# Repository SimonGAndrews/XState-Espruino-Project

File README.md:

# XState-Espruino-Project

This public umbrella repository records the development of three approaches to
running state machines and statecharts on
[Espruino](https://www.espruino.com/), informed by
[XState](https://github.com/statelyai/xstate).

It retains the flat FSM baseline, the JavaScript FSMPlus engine, shared
examples, architectural decisions, and the history connecting those
approaches. The native C engine, XFSM, matured through this project and is now
developed independently in the standalone
[`SimonGAndrews/Espruino-XFSM`](https://github.com/SimonGAndrews/Espruino-XFSM)
repository.

This repository remains public as a project history, comparison point, and
navigation hub. Each implementation direction retains its own behavioural
authority and development lifecycle.

## Current Status

XFSM is the current active development focus. Its source, specifications,
tests, evidence, examples, and integration guidance are maintained in the
standalone Espruino-XFSM repository. Its
[implementation status](https://github.com/SimonGAndrews/Espruino-XFSM/blob/main/docs/implementation-status.md)
records current qualification and development work.

Stage 1 remains the compact flat embedded baseline. FSMPlus remains a working
JavaScript hierarchical engine that can be deployed without a custom Espruino
firmware build. Moving XFSM to its own repository does not replace or deprecate
either direction.

The [current project context](docs/project-context.md) identifies the authority
and compatibility references for all three directions.

## Project Outcomes

The stage numbers describe the order in which the approaches arose. They do
not define a replacement sequence.

| Direction | Outcome | Current position |
| --- | --- | --- |
| [Stage 1: `xstate-fsm-espruino`](projects/xstate-fsm-espruino/) | Compact flat FSM adapted from `@xstate/fsm` for Espruino | Retained as a separate Git submodule and embedded baseline |
| [Stage 2: `xstate-fsmPlus`](projects/xstate-fsmPlus/) | Hierarchical JavaScript engine supporting compound states | Working parallel implementation maintained in this repository |
| [Stage 3: `Espruino-XFSM`](https://github.com/SimonGAndrews/Espruino-XFSM) | Specification-led native C hierarchical engine exposed through Espruino's `XFSM` module | Active development in its standalone repository |

Together, these approaches explored the trade-offs between deployment
simplicity, statechart capability, memory use, execution cost, and integration
with Espruino internals.

## What Remains Here

The umbrella repository retains:

- the Stage 1 Git submodule and its separate history
- the canonical FSMPlus implementation, tests, and status documents
- shared application examples and scenario-driven testing material
- architectural decisions and the background to the three approaches
- the XState v4 reference runner used by Stage 1 and FSMPlus work
- an archived XState v4.38.3 source tree for historical reference
- the XFSM journey and relocation record

Material shared by the projects is evidence or a reusable input. It does not
automatically change the behavioural contract of another implementation.

## XFSM Relocation

Current XFSM work belongs in
[`SimonGAndrews/Espruino-XFSM`](https://github.com/SimonGAndrews/Espruino-XFSM).
The standalone repository is the source of truth for the native library,
Profile 2 specification, tests, recorded evidence, examples, and development
workflow. Its canonical `xfsm/` library is exported unchanged into Espruino's
`libs/xfsm/` directory for integration builds.

This umbrella retains a permanent
[`projects/Xstate-fsm-c/`](projects/Xstate-fsm-c/) placeholder explaining the
project's journey and current location. The last complete umbrella copy is
preserved by the
[`xfsm-umbrella-snapshot-final`](https://github.com/SimonGAndrews/XState-Espruino-Project/tree/xfsm-umbrella-snapshot-final/projects/Xstate-fsm-c)
tag.

## Testing And Authority

Testing across the umbrella project is scenario-driven and trace-based, using
deterministic event sequences and observable state, action, and context
results. The shared [testing strategy](docs/governance/testing-strategy.md)
describes this approach.

Each implementation decides which shared scenarios it adopts and which
external references define its expected behaviour:

- Stage 1 is governed by its submodule source, tests, and documentation.
- FSMPlus is governed by its implementation, tests, status, and applicable
  architectural decisions in this repository.
- XFSM is governed by the standalone Profile 2 specification and its
  incorporated Profile 1 and history requirements.

The [project context](docs/project-context.md) is the complete navigation and
authority guide.

## Documentation

- [Current project context and authority](docs/project-context.md)
- [Background and evolution](docs/governance/background.md)
- [Testing strategy and issue ownership](docs/governance/testing-strategy.md)
- [FSMPlus status and backlog](docs/governance/fsmPlus-status-01.md)
- [Architectural decisions](docs/decisions/)
- [Reference links](docs/references/links.md)
- [XFSM project overview](https://github.com/SimonGAndrews/Espruino-XFSM#readme)
- [XFSM Profile 2 specification](https://github.com/SimonGAndrews/Espruino-XFSM/blob/main/docs/specification-profile-2.md)
- [XFSM implementation status](https://github.com/SimonGAndrews/Espruino-XFSM/blob/main/docs/implementation-status.md)
- [XFSM Espruino integration workflow](https://github.com/SimonGAndrews/Espruino-XFSM/blob/main/docs/espruino-integration.md)

## Licensing

This umbrella repository contains independently licensed projects, an upstream
source archive, and a Git submodule. See [LICENSING.md](LICENSING.md) for the
path-to-licence map. The retained Xstate-fsm-c record and tagged snapshot are
licensed under MPL-2.0. The standalone Espruino-XFSM repository publishes its
own path-based licensing map.

## Acknowledgements

- **Espruino** - the [open-source JavaScript runtime](https://www.espruino.com/)
  and community that make embedded JavaScript development possible.
- **XState and Stately** - the statechart model, tooling, and API patterns from
  [XState](https://github.com/statelyai/xstate) and
  [Stately](https://stately.ai/) that informed the three project directions.

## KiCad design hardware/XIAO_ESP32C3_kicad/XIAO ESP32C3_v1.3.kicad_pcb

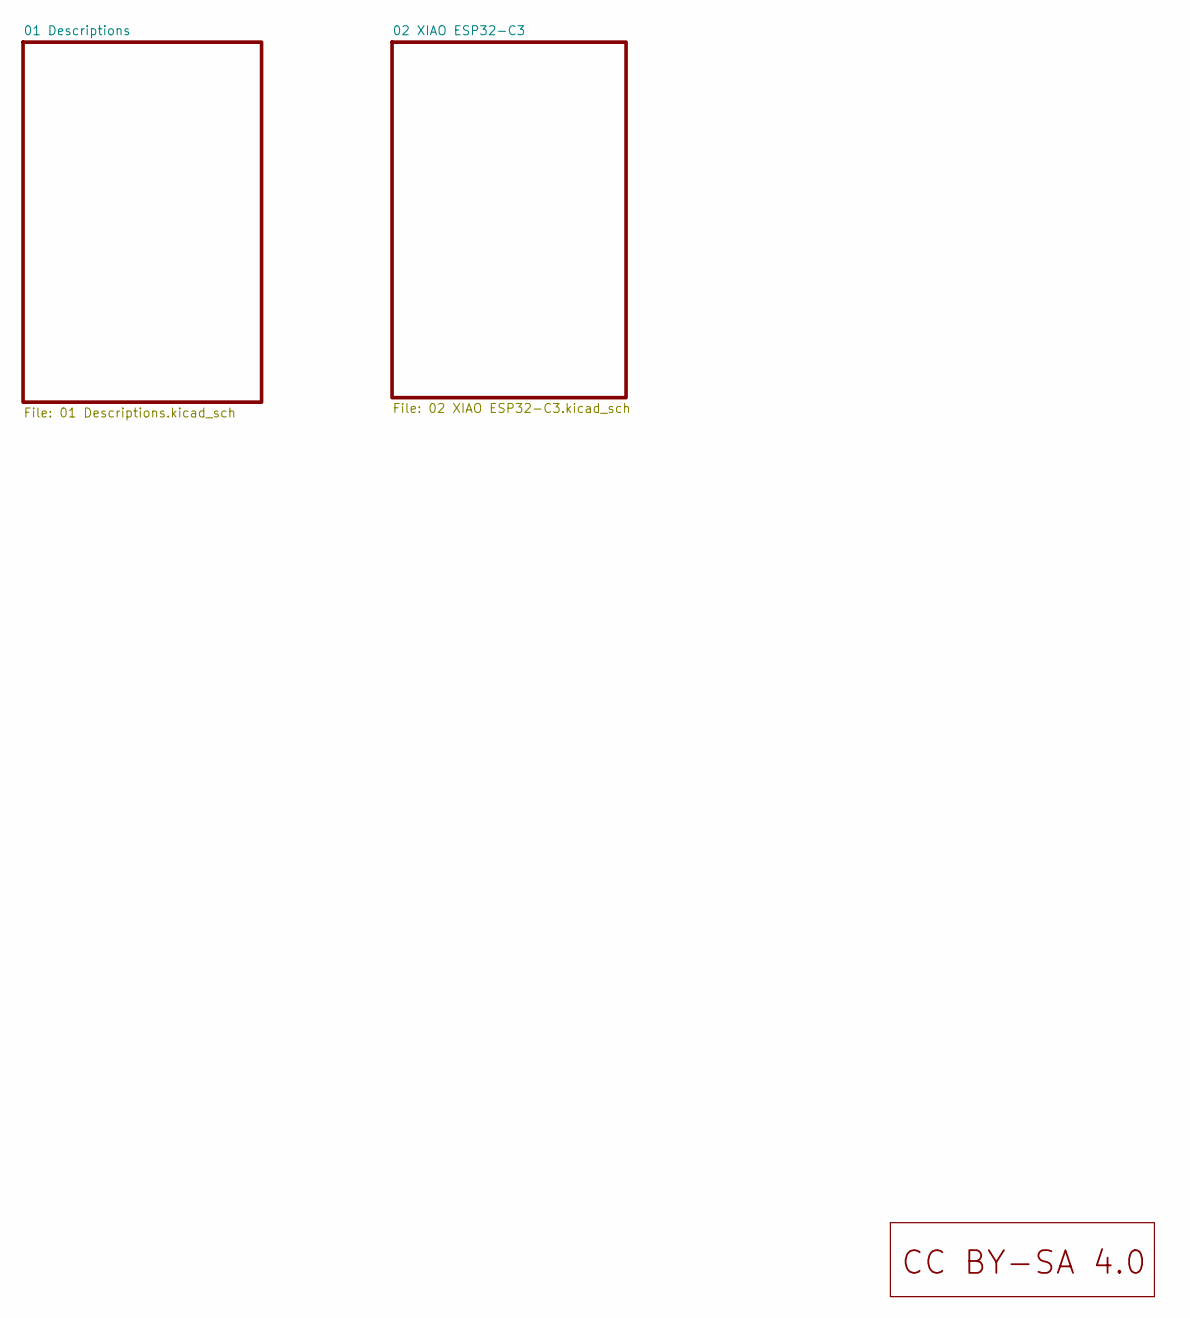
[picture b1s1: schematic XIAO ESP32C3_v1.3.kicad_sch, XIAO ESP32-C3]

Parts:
U3: LOGO_CC_BY-SA_4.0

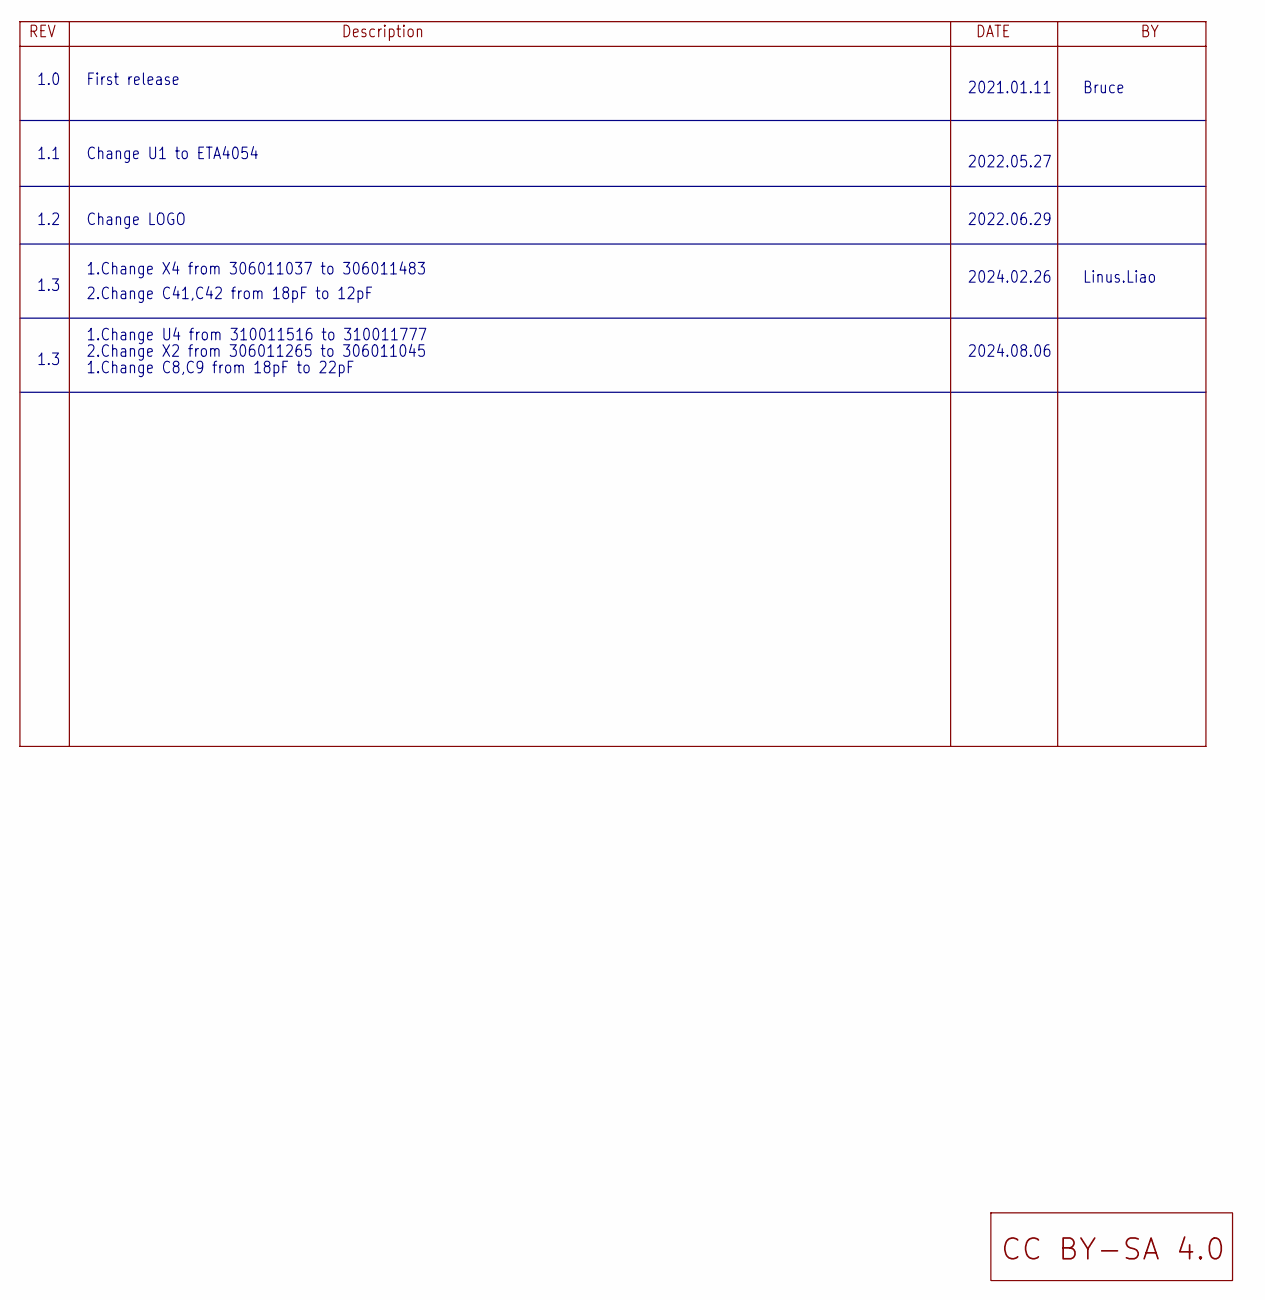
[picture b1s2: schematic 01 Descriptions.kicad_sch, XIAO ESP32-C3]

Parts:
U5: LOGO_CC_BY-SA_4.0

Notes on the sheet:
1.0
1.Change X4 from 306011037 to 306011483
1.Change U4 from 310011516 to 310011777
1.3
1.2
2.Change C41,C42 from 18pF to 12pF
2022.06.29
2022.05.27
Linus.Liao
2.Change X2 from 306011265 to 306011045
Bruce
2024.08.06
1.1
Change LOGO
2024.02.26
2021.01.11
First release
Change U1 to ETA4054
1.Change C8,C9 from 18pF to 22pF

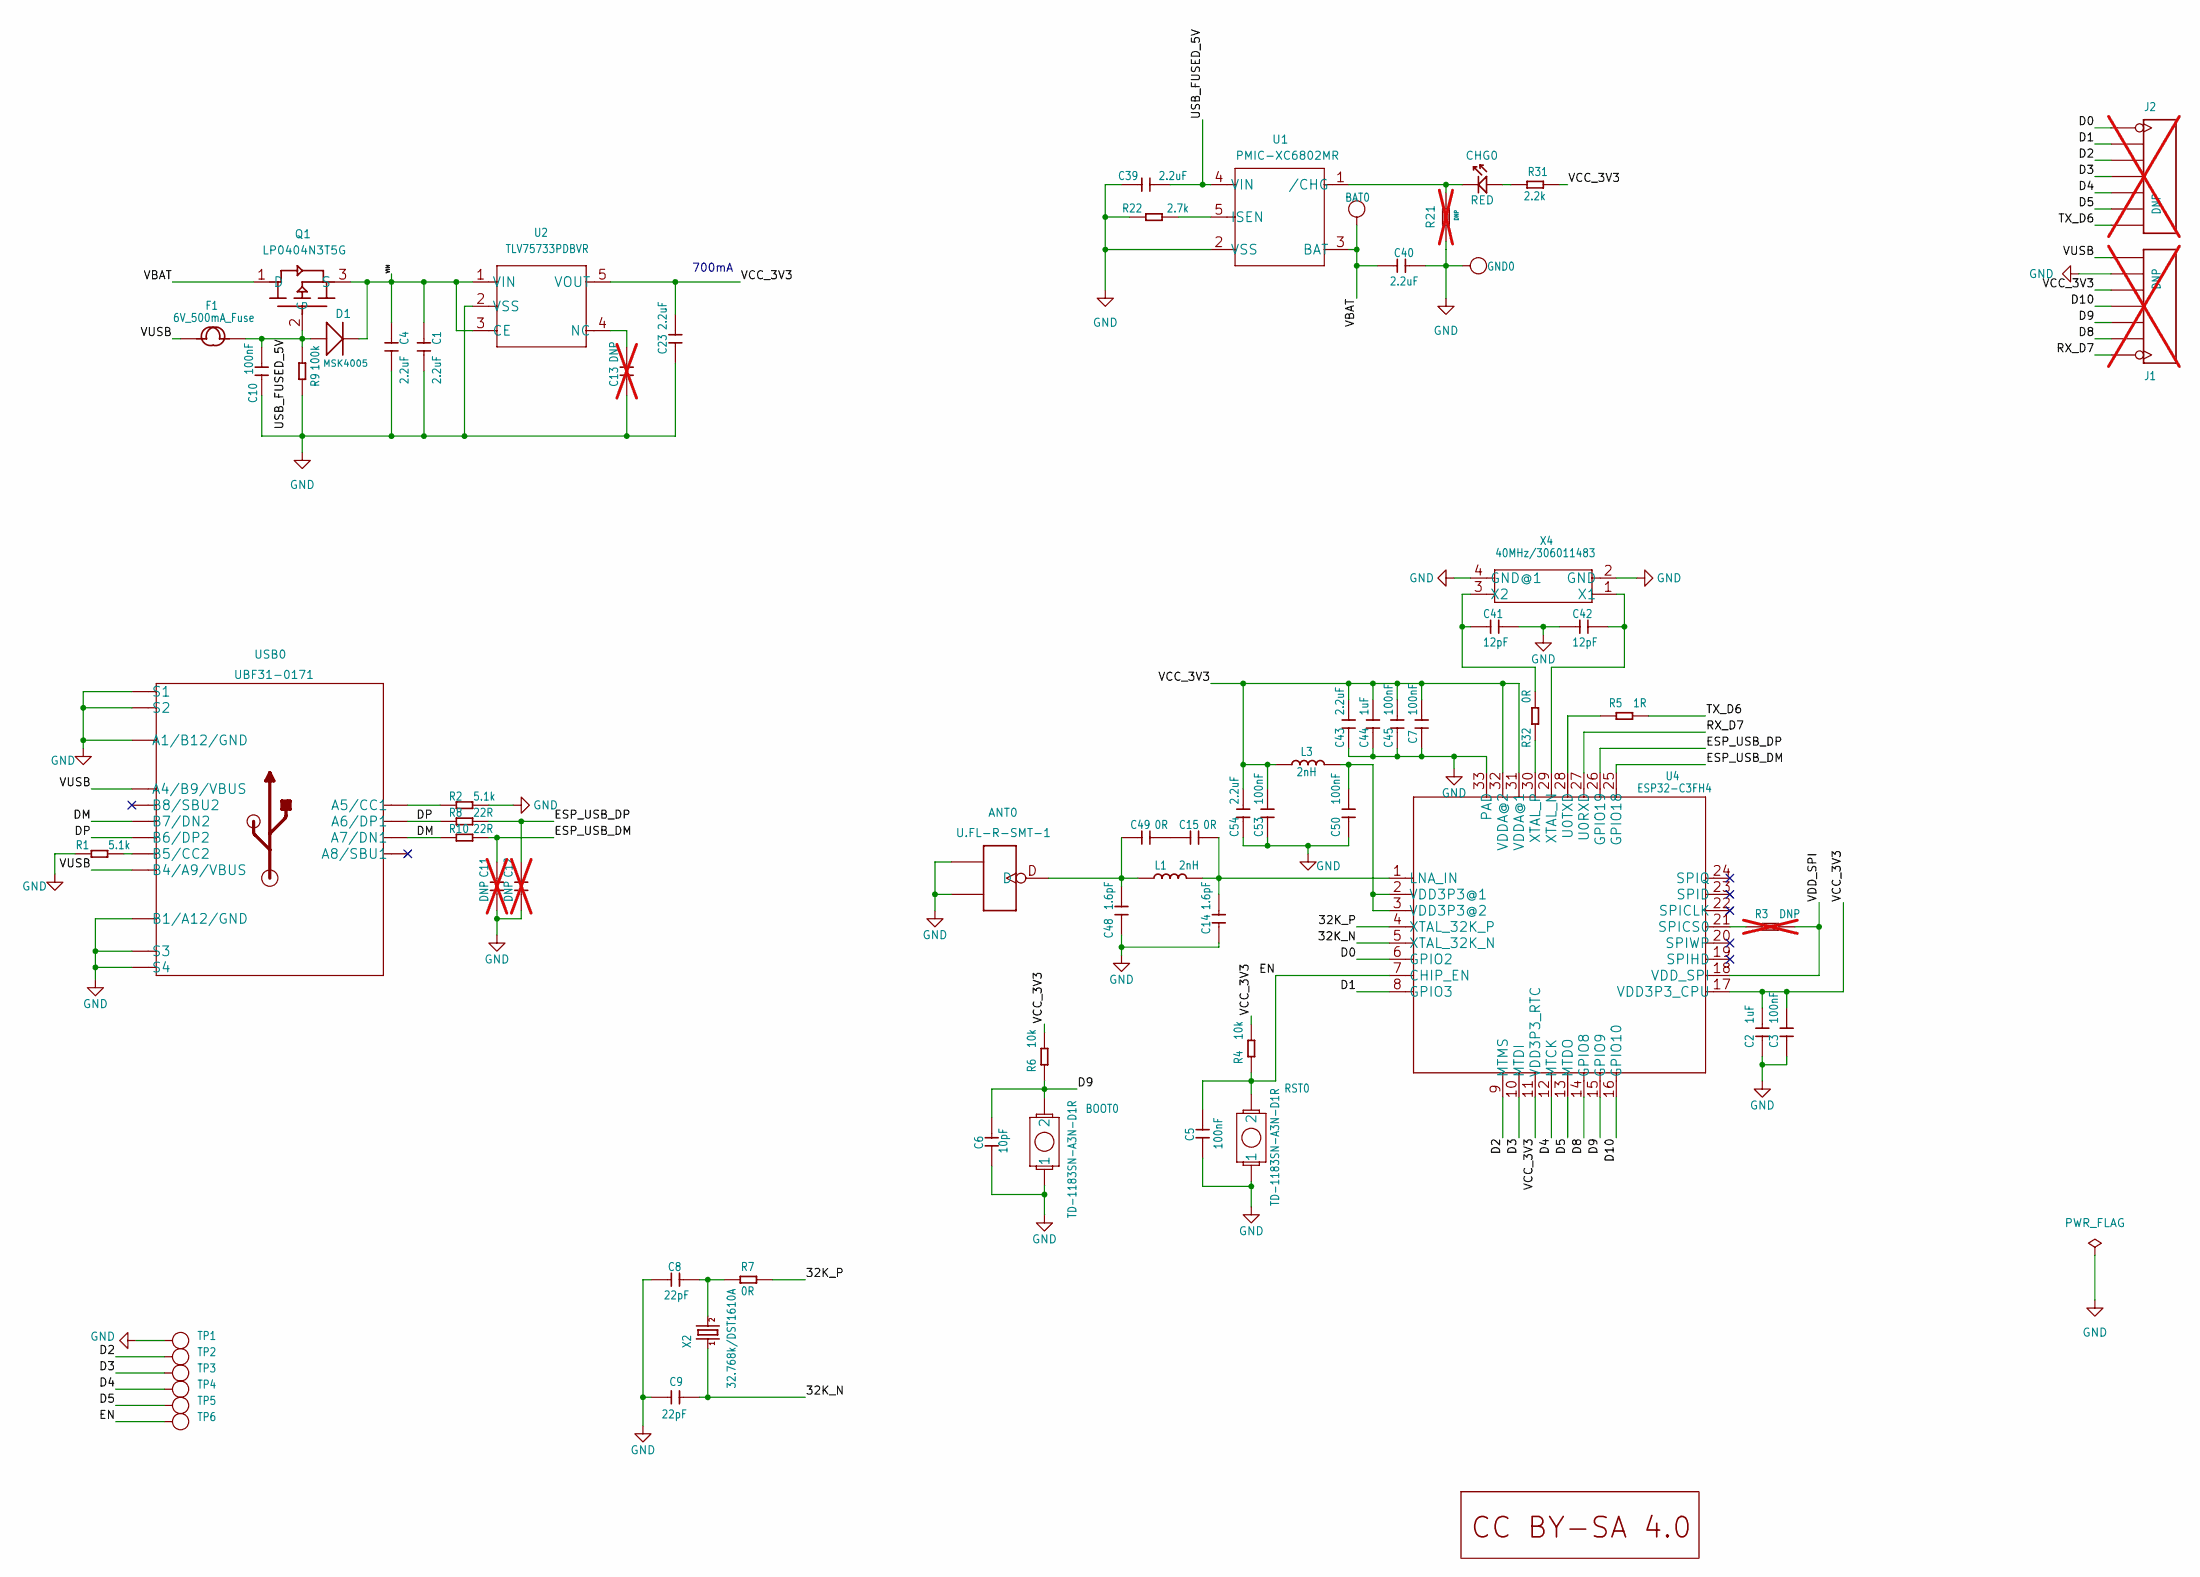
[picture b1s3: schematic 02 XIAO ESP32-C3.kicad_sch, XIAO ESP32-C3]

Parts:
ANT0: U.FL-R-SMT-1; U-FL3P-SMD-2.6X2.6X1.0MM
BAT0: DNP; TP-80X40MIL
BOOT0: TD-1183SN-A3N-D1R; BUTTON_TD1183SA
C1, C4, C23, C39, C40, C43, C54: 2.2uF; C0201
C2, C44: 1uF; C0201
C3, C5, C7, C10, C45, C50, C53: 100nF; C0201
C6: 10pF; C0201
C8, C9: 22pF; C0201
C11, C12, C13: DNP; C0201; not fitted
C14, C48: 1.6pF; C0201
C15, C49: 0R; C0201
C41, C42: 12pF; C0201
CHG0: RED; LED-0402
D1: MSK4005; SOD-523
F1: 6V_500mA_Fuse; F0603
GND0: DNP; TP-80X40MIL
J1, J2: DNP; H7-HALF-HOLE-2.54; not fitted
L1, L3: 2nH; L0201
Q1: LP0404N3T5G; PMOS_1.0_0.6_0.35MM
R1, R2: 5.1k; R0201
R3, R21: DNP; R0201; not fitted
R4, R6: 10k; R0201
R5: 1R; R0201
R7, R32: 0R; R0201
R8, R10: 22R; R0201
R9: 100k; R0201
R22: 2.7k; R0201
R31: 2.2k; R0201
RST0: TD-1183SN-A3N-D1R; BUTTON_TD1183SA
TP1, TP2, TP3, TP4, TP5, TP6: DNP; TP-D45MIL
U1: PMIC-XC6802MR; SOT-25
U2: TLV75733PDBVR; SOT-25
U4: ESP32-C3FH4; QFN32G-0.5-5X5MM
U6: LOGO_CC_BY-SA_4.0
USB0: UBF31-0171; USB2.0-TYPE-C
X2: 32.768k/DST1610A; X2-SMD-1.6X1.0X0.5MM
X4: 40MHz/306011483; X4-SMD-2.0X1.6X0.5MM

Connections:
32K_N: C9.1, U4.5 (XTAL_32K_N), X2.1
32K_P: R7.1, U4.4 (XTAL_32K_P)
D0: J2.1, J2.13 (1), U4.6 (GPIO2)
D1: J2.2, J2.14 (2), U4.8 (GPIO3)
D2: J2.3, J2.15 (3), TP2.T, U4.9 (MTMS)
D3: J2.4, J2.16 (4), TP3.T, U4.10 (MTDI)
D4: J2.5, J2.17 (5), TP4.T, U4.12 (MTCK)
D5: J2.6, J2.18 (6), TP5.T, U4.13 (MTDO)
D8: J1.2, J1.14 (2), U4.14 (GPIO8)
D9: BOOT0.2, C6.2, J1.3, J1.15 (3), R6.1, U4.15 (GPIO9)
D10: J1.4, J1.16 (4), U4.16 (GPIO10)
DM: R10.1, USB0.A7 (A7/DN1), USB0.B7 (B7/DN2)
DP: R8.1, USB0.A6 (A6/DP1), USB0.B6 (B6/DP2)
EN: C5.2, R4.1, RST0.2, TP6.T, U4.7 (CHIP_EN)
ESP_USB_DM: C11.2, R10.2, U4.25 (GPIO18)
ESP_USB_DP: C12.2, R8.2, U4.26 (GPIO19)
GND: ANT0.GND1, ANT0.GND2, BOOT0.1, C1.2, C2.1, C3.1, C4.2, C5.1, C6.1, C7.1, C8.2, C9.2, C10.1, C11.1, C12.1, C13.1, C14.1, C23.1, C39.1, C40.2, C41.2, C42.2, C43.1, C44.1, C45.1, C48.1, C50.1, C53.1, C54.1, GND0.1, J1.6, J1.18 (6), R1.1, R2.2, R9.1, R21.2, R22.2, RST0.1, TP1.T, U1.2 (VSS), U2.2 (VSS), U4.33 (PAD), USB0.A1_B12 (A1/B12/GND), USB0.B1_A12 (B1/A12/GND), USB0.S1, USB0.S2, USB0.S3, USB0.S4, USB0.S5 (S1), USB0.S6 (S2), X4.2 (GND), X4.4 (GND@1)
unnamed: R2.1, USB0.A5 (A5/CC1)
unnamed: R1.2, USB0.B5 (B5/CC2)
unnamed: R3.1, U4.21 (SPICS0)
unnamed: C8.1, R7.2, X2.2
unnamed: C13.2, U2.4 (NC)
unnamed: C15.2, C49.1
unnamed: R22.1, U1.5 (ISEN)
unnamed: CHG0.+, R31.2
unnamed: C14.2, C15.1, L1.2, U4.1 (LNA_IN)
unnamed: C41.1, R32.2, X4.3 (X2)
unnamed: C42.1, U4.29 (XTAL_N), X4.1 (X1)
unnamed: ANT0.D, C48.2, C49.2, L1.1
unnamed: R5.2, U4.28 (U0TXD)
unnamed: C50.2, L3.2, U4.2 (VDD3P3@1), U4.3 (VDD3P3@2)
unnamed: R32.1, U4.30 (XTAL_P)
RX_D7: J1.1, J1.13 (1), U4.27 (U0RXD)
TX_D6: J2.7, J2.19 (7), R5.1
USB_FUSED_5V: C10.2, C39.2, D1.+, F1.2, Q1.2 (G), R9.2, U1.4 (VIN)
VBAT: BAT0.1, C40.1, Q1.1 (D), U1.3 (BAT)
VCC_3V3: C2.2, C3.2, C7.2, C23.2, C43.2, C44.2, C45.2, C53.2, C54.2, J1.5, J1.17 (5), L3.1, R4.2, R6.2, R31.1, U2.5 (VOUT), U4.11 (VDD3P3_RTC), U4.17 (VDD3P3_CPU), U4.31 (VDDA@1), U4.32 (VDDA@2)
VDD_SPI: R3.2, U4.18 (VDD_SPI)
VIN: C1.1, C4.1, D1.-, Q1.3 (S), U2.1 (VIN), U2.3 (CE)
VUSB: F1.1, J1.7, J1.19 (7), USB0.A4_B9 (A4/B9/VBUS), USB0.B4_A9 (B4/A9/VBUS)
~CHG: CHG0.-, R21.1, U1.1 (/CHG)

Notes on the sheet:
700mA

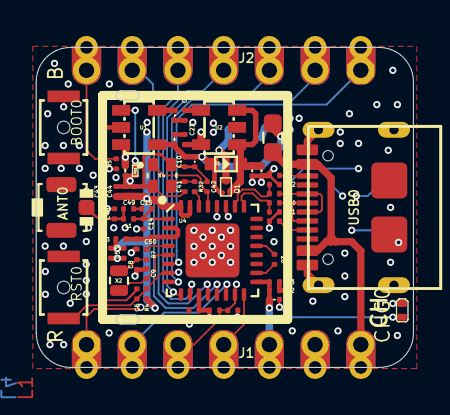
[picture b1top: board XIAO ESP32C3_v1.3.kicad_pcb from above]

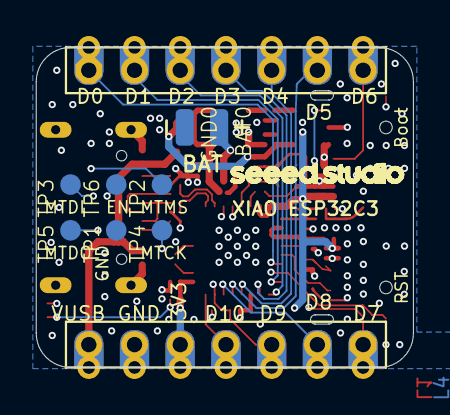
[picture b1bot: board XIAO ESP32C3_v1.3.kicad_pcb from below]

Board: 4 copper layers, 21.0 x 17.8 mm, 68 parts (9 on the bottom side), 41 nets.

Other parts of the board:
U$2: LOGO-SEEED-NEW-1X9.6MM

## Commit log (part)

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2026-02-06 Add xstate-fsm-Espruino as submodule (baseline JS engine)
2026-02-06 Add initial project documentation (background, references, ADR framework, testing strategy)
2026-02-06 ADR-0001: Exclude parallel states from initial implementations
2026-02-06 Move xstate-fsm-Espruino submodule under projects/
2026-02-06 Structure Subprojects
2026-02-07 Scaffold FSMPlus subproject with canonical README and archived reference material
2026-02-07 Import FSMPlus baseline (V15) from xstatePlusDev
2026-02-07 Add FSMPlus V15 snapshot for baseline provenance
2026-02-07 Add FSMPlus V16 snapshot for comparison
2026-02-07 Codex-handover.md created with ADRs ready to move to codex in vscode.
2026-02-07 Fix missing findTransition helper in FSMPlus engine
2026-02-07 Document V15 snapshot findTransition omission
2026-02-07 Add greenhouse scenario and split Node/Espruino test harness
2026-02-07 Handle guarded transition arrays during parent fallback
2026-02-09 Move scenarios to root examples and update test harness
2026-02-09 Add XState v4 truth runner scaffold and adapter
2026-02-09 Add usage headers to scenario and runner files
2026-02-09 Add test runner READMEs
2026-02-09 Add pinned XState v4 references
2026-02-09 Add tooling compatibility ADR and stately import stub
2026-02-09 Doc structure tidy-up
2026-02-09 Document FSMPlus flow comments and status summary
2026-02-09 Implement MVHE entry/exit ordering and add hierarchy test
2026-02-09 Add MVHE edge-case scenarios and v4 truth runners
2026-02-09 Rename scenario and runner filenames to underscores for Espruino
2026-02-09 Rename FSMPlus source file to underscore and update references
2026-02-09 Use flash module names in Espruino test runners
2026-02-09 Add simple Espruino CLI helper
2026-02-09 Add Espruino trace printing and diff helper
2026-02-10 Enhance Espruino test helper with timestamped results
2026-02-10 Print prepared results file path in Espruino helper
2026-02-10 Document Espruino test workflow and improve helper output
2026-02-10 Update FSMPlus evolution notes and clarify section comments
2026-02-10 Add initial entry actions to FSMPlus start state
2026-02-10 Resolve non-leaf start states and apply entry actions
2026-02-10 Align matches() with ancestor semantics
2026-02-10 Add multi-level guarded parent fallback scenario
2026-02-10 Add context trace lines to greenhouse scenario
2026-02-10 Allow diff_trace to target timestamped results
2026-02-10 Harden espruino tools for dashed scenarios and trace markers
2026-02-10 Add start_matches scenario for start override and matches
2026-02-10 Interactive gaps review
2026-02-10 Interactive Espruino Examples
2026-02-10 Add withConfig design note
2026-02-10 Add withConfig support and withconfig_basic scenario
2026-02-10 Document withConfig support and references
2026-02-10 Add umbrella README and link background context
2026-02-11 Fix LCCA set membership for 'on' state names and validate action execution patterns
2026-02-11 Refine Espruino CLI workflow docs and refresh FSMPlus status note
2026-02-11 Rationalize v15.2 docs structure and Espruino test operations
2026-02-12 Finalize v15.2 handover and canonical governance references
2026-02-12 Add v15.3 normative decision baseline
2026-02-12 Finalize v15.3 handover cross-references
2026-02-15 docs: add Espruino references and ADR-0008 performance strategy
2026-02-15 Created myXstateNaming.md to support testing
2026-02-16 docs+tests: add stately compatibility ADRs and baseline scenario
2026-02-16 perf: add GPIO bench harness and measurement documentation
2026-02-16 Update ADR-0009 and ADR-0010 after experimenting with vscode xstate editor and observed gaps in xstate fsmPlus
2026-02-18 docs(gh01): add hardware spec and antenna guidance
2026-02-19 hardware/gh01: structure KiCad projects into versioned folders
2026-02-19 hardware/gh01: add V1 hardware spec, wiring diagrams, and XIAO reference files
2026-02-19 hardware/gh01: finalize V2 schematic baseline with clean ERC and matrix
2026-02-20 hardware/gh01: add AZ-Delivery PSU symbol and schematic updates
2026-02-20 GH01 V2 design updates
2026-02-20 GH01 split AC/LV scaffold and interface validation
2026-02-22 GH01: finalize LV schematic, test points, and spec alignment
